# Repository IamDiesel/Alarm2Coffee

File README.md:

# Power on your Philips 2200 Coffeemachine when your smartphone-alarm goes off - via Raspberry Pi and Home-Assistant #
The following readme describes how to setup a raspberry pi / philips 2200 coffeemachine home assistant automation from scratch (incl. setting up home assistant on a Raspberry Pi5). Btw. thanks to https://github.com/TillFleisch/ESPHome-Philips-Smart-Coffee who gave me some inspiration / information on the coffee machine's UART-protocol.
This project is also capable of displaying the current coffeemachine state and remotly operating the coffeemachine via a smartphone's home assistant app:

### Requirements: ###
- Coffee-Machine: Philips 2200
- MITM (inject & passthrough): Inject coffee selection commands and read current coffee configuration
- Use home assistant for automation and hub to the smartphone alarm
- Additional Fail-Safe mechanism in case RPi is dead and  the MITM configuration must be bridged

### Components used: ###
- Raspberry Pi5 + SD Card
- PicoFlex 90325-0008 socket
- Molex 92315-0815, Picoflex, ribbon cable 150mm
- AZDelivery 3 x 4-Relais Modul 5V
- LUCKFOX DSI Capacitive 7 inch Touch Screen with Case
- Jumper Wire / cables / glue / screws / ...
- If Home Assistant should be connected via wifi: Brostrend AX1800 (External USB Wifi Antenna)

## Install home assistant on Raspberry Pi 5 ##
- Use Pi Imager to flash SD card (see https://developbyter.com/home-assistant-auf-raspberry-pi-installieren-und-einrichten/) 
- create empty file called "ssh" on sd card "bootfs"
- tell router to give RPi a constant IP address
- connect via ssh to RPi (ssh user@ipadress)
- update: sudo apt-get update && sudo apt-get upgrade -y
- install dependencies:
  - sudo apt-get install jq wget curl avahi-daemon udisks2 libglib2.0-bin network-manager dbus apparmor -y
  - sudo apt-get install systemd-journal-remote
- reboot: sudo reboot
- deactivate mac address randomisation:
  - sudo nano /etc/NetworkManager/conf.d/100-disable-wifi-mac-randomization.conf
  - Content:

~~~
[connection]
wifi.mac-address-randomization=1
[device]
wifi.scan-rand-mac-address=no
)
~~~

- install docker & add user:
  
~~~
curl -fsSL https://get.docker.com -o get-docker.sh
sudo sh get-docker.sh
docker –version
sudo usermod -aG docker <user>
~~~

- Download OS-Agent on raspberry pi: wget https://github.com/home-assistant/os-agent/releases/download/1.6.0/os-agent_1.6.0_linux_aarch64.deb
- install: sudo dpkg -i os-agent_1.6.0_linux_aarch64.deb

- install additional dependencies:

~~~
sudo apt install \
apparmor \
bluez \
cifs-utils \
curl \
dbus \
jq \
libglib2.0-bin \
lsb-release \
network-manager \
nfs-common \
systemd-journal-remote \
systemd-resolved \
udisks2 \
wget -y
~~~

- install home assistant superviced (https://github.com/home-assistant/supervised-installer/releases/download/2.0.0/homeassistant-supervised.deb)
  - sudo dpkg -i homeassistant-supervised.deb
  - during installation: choose raspberrypi5-64
  - reboot
- open home assistant in your browser: <ipadress_of_pi>:8123
- download and install smartphone app via QR-Code
- Show home assistant on startup on the 7" display:
  - configure autostart: sudo nano /etc/xdg/lxsession/LXDE-pi/autostart
    - add the following lines:
      
~~~
@unclutter
@xset s off
@xset -dpms
@xset s noblank
@chromium-browser --noerrdialogs --check-for-update-interval=31536000 --disable-infobars --kiosk http://127.0.0.1:8123/
~~~
  if you want to keep a 5min display off timer, use the following settings:
~~~
@unclutter
@xset s off
@xset -dpms
@xset s 300 300
@xset s blank
@chromium-browser --noerrdialogs --check-for-update-interval=31536000 --disable-infobars --kiosk http://127.0.0.1:8123/
~~~

  - activate autologin on pi

~~~
cd /usr/share/hassio/homeassistant/
sudo nano configuration.yaml
~~~

  - add the following lines
    
~~~

homeassistant:
  auth_providers:
    - type: homeassistant
    - type: trusted_networks
      trusted_networks:
        - 192.168.2.0/24  # Example network, adjust to your network range
        - fd00::/8
      trusted_users:
        127.0.0.1: 6a24b8e59e2c45328cd1s97ds0b71221  # Map the IP address to the user ID
        192.168.2.43: 6a24b8249e22445x1cd1797123471221  # Map the IP address to the user ID
      allow_bypass_login: true
  ~~~
  
- install 7inch display (https://wiki.luckfox.com/):
  - sudo nano /boot/config.txt
  - add the following lines:
 
~~~
dtoverlay=vc4-kms-v3d
dtoverlay=vc4-kms-dsi-7inch
~~~
## Install Wifi Antenna ##
Installation guide see https://linux.brostrend.com/
For me, the command from the installation guide threw an error.
Command:
~~~
 sh -c 'wget linux.brostrend.com/install -O /tmp/install && sh /tmp/install'
~~~
Error:
~~~
Setting up initramfs-tools (0.142+rpt3+deb12u1) ...
update-initramfs: deferring update (trigger activated)
Processing triggers for initramfs-tools (0.142+rpt3+deb12u1) ...
update-initramfs: Generating /boot/initrd.img-6.6.62+rpt-rpi-v8
mkinitramfs: failed to determine device for /
mkinitramfs: workaround is MODULES=most, check:
grep -r MODULES /etc/initramfs-tools

Error please report bug on initramfs-tools
Include the output of 'mount' and 'cat /proc/mounts'
update-initramfs: failed for /boot/initrd.img-6.6.62+rpt-rpi-v8 with 1.
dpkg: error processing package initramfs-tools (--configure):
 installed initramfs-tools package post-installation script subprocess returned error exit status 1
Errors were encountered while processing:
 initramfs-tools
E: Sub-process /usr/bin/dpkg returned an error code (1)
Aborting, command failed: apt install --reinstall --yes --no-install-recommends ./rtl8852bu-dkms.deb

===================================================
 ERROR: The driver was NOT successfully installed!
===================================================
1) Please select ALL the text in this terminal, then right click with the
   mouse and select Copy, and finally paste all the text in an email to:
   support@brostrend.com
2) Please also attach this autogenerated log file to the email:
   /tmp/troubleshooting.txt
   If you want to view it, run:
   xdg-open /tmp/troubleshooting.txt
3) Some common issues are documented in:
   https://linux.brostrend.com/troubleshooting/
~~~
Solution:
~~~
sudo nano /etc/initramfs-tools/initramfs.conf
~~~
And set „MODULES=dep“ to „MODULES=most“.
Next, the wifi interface needs to be configured:
- deactivate wlan0: sudo ip link set wlan0 down
- Router: remove static ip for old interface and set static ip for the new interface (e.g. 192.168.2.43)
- In Home Assistant: Go to settings->system->network.
  - Reset configuration for wlan0
  - Set static ip for wlan1
- Configure wifi connection:
  - remove all wlan0 profiles (in GUI top right corner, click on the wifi symbol and delete all wlan0 profiles) 
  - sudo nmtui
  - edit connection
  - select wifi->preconficured --> hit "edit"
  - Find the wlan1 device name (for me it is wlxc83a35b569cd (C8:3A:35:B5:69:CD)
  - Enter SSID
  - Enter WIFI-password
  - set manual ip adress: 192.168.2.43/24
  - set Gateway: your routers ip
  - set DNS servers: your routers ip
 
- If chromium doest start on boot: rm -rf ~/.config/chromium/Singleton*

## configure home assistant ##
### Create entities (German) ###
Create entities (Einstellungen -> Geräte und Dienste -> Helfer)

### Create Automations (German) ###

### setup alarm (Android) ###
- Open the Home Assistant App menu and select Settings
- Go to Companion App
- Select Manage Sensors
- Find the Next Alarm sensor
- Enable the Next Alarm sensor
- Create automation: „Einstellungen“->“Automatisierung & Szenen“->“Automatisierung erstellen““Neue Automatisierung“
  - Auslöser hinzufügen: “Andere Auslöser“-->“Template“
  - Template code:
  
   ~~~
    {{(now()+timedelta(0,60)).strftime('%a %h %d %H:%M %Z %Y') == (((state_attr('sensor.pixel_9_pro_next_alarm', 'Time in Milliseconds') | int / 1000) ) | timestamp_custom('%a %h %d %H:%M %Z %Y'))}}
   ~~~
   
  - add action:

### setup alarm (iOs) ###
The focus sensor can be used to determine when the alarm went off.
- Create iOS shortcut named "HAss focus": deactivate focus
- Create iOS automation that executes the "Hass focus" everytime an alarm goes off
Now the companion app focus sensor of the iOS device can be used to trigger automations in Home-Assistant
- Create Home-Assistant automation:

# Disassemble coffee machine #
The coffee machine's display can be disassembled using a plastic tool.

The wiring between display and mainboard is as follows:

Communication is run via UART @115200
The state of the coffeemachine ist sent from the mainboard to the display. The button events are sent from the display to the mainboard.

# Communication #
## Mainboard -> Display

## Display -> Mainboard

### On / Off ###

~~~
On / Off Beep: d5 55 0a 00 00 03 02 00 00 00 32 25
Power on without cleaning cycle: d5 55 01 00 00 03 02 00 00 00 19 10	
Power Off no Cleaning cycle?: d5550000000302010000210c
~~~

### Drink Selection: ###

~~~
Select Nothing: 		d5 55 00 00 00 03 02 00 00 00 2d 01
Select Espresso:	d5 55 00 00 00 03 02 02 00 00 35 1a 	Nachricht wird 13x gesendet
perl -e 'print pack "H*", "d5550000000302020000351a"' > /dev/ttyUSB2

Hot Water:		d5 55 00 00 00 03 02 04 00 00 1d 36
Select Coffee:		d5 55 00 00 00 03 02 08 00 00 05 2b	Nachricht wird 8x gesendet
Steam:			d5 55 00 00 00 03 02 10 00 00 35 11	Nachricht wird 32x gesendet
~~~

### Settings: ###

~~~

d5 55 00 00 00 03 02 00 02 00 35 18	Bean Size
d5 55 00 00 00 03 02 00 04 00 1c 32	Coffee Size
Play:
d5 55 00 00 00 03 02 00 00 01 25 05 	Play-Button (espresso, 39x)
perl -e 'print pack "H*", "d55500000003020000012505"' > /dev/ttyUSB2
~~~

For both mainboard messages and display messages the CRC algorithm is currently unknown. So it might be necessary to record the messages individually.

## Connect relais, UART and power ##

The relayboard 1 is used as a failsafe when the pi does not power on. In that case the UART connection will be without the MITM and therby the mainboard is directly connected to the display. When the relay is activated the raspberry pi acts as MITM between mainboard and display.
Relayboard 2 is used to reset the display when activated via power on command incection. A power cycle will activate the display. This relay is also failsafe for the case, that RPi is powered off, since Display GND is connected to the Relay-Normally-Closed Pin and Relay-Common is connected to the Mainboard GND.
Here is the connection diagram:

## Activate UART2/3 and GPIO on RPi5 & ## 

Add the following lines via "sudo nano /boot/config.txt":

As a result the GPIO configuration will be as follows:
- ttyAMA2	Display	Pin 7 (GPIO 4)	TX
- ttyAMA2	Display	Pin 29 (GPIO 5)	RX
- ttyAMA3	Mainboard	Pin 24 (GPIO 8)	TX
- ttyAMA3	Mainboard	Pin 21 (GPIO 9)	RX

- In order to use GPIO on RPi5 another package is required: .coffee/bin/pip install rpi-lgpio
- It could be necessary to uninstall the RPi GPIO first: .coffee/bin/pip uninstall Rpi.GPIO

## Setup Home Assistant API / install the required python packages ##

- Create a longliving HAss token in HAss: Profil->Sicherheit
  - safe this token in a file called "HASS_Token.py" with: token = "asdjalksdjkasjdklasjd your token asdlkalösdkaölsd"
- Create venv:  python3 -m venv .coffee
- install Home assistant: .coffee/bin/pip install homeassistant_api
- install pyserial: .coffee/bin/pip install pyserial

## Home Assistant WIFI Stability Issues ##
Home Assistant started beeing offline from time to time. Where the device was not reachable via ssh or the home assistant app.
The only thing that seemed to help was a wifi reset. So I wrote a little script that (e.g.) pings the local router. In case the router is not reachable the script will reset wifi, making the HAss available again.

## Finish ##

- Thats it. Now run Philips_2200.py and the RPI will inject the respective display commands, when the respective Home Assistant buttons are pushed. If no button is pushed, the RPi will forward all messages from display to mainboard and vice versa. In Addition a alarm will trigger a power on command sent to the coffee machine.
- the relay boards fit nicely behind the display. I glued screws on the backside of the display module in order to fit the relay boards to the display.
- In order to run the python script on startup the following lines can be added to rc.local via sudo nano /etc/rc.local:
~~~
sudo bash -c '/home/youruser/.coffee/bin/python3 /home/youruser/Documents/philips_pi/Philips_2200.py > /home/fuchsi/Documents/philips_pi/alarm2coffee.log 2>&1' &
~~~
Of course the path must be set to your local Philips_2200.py. In addition Wifi_Reset.py must be in the same folder as Philips_2200.py.
- Also a dashboard can be created in order to interact with the coffeemachine via smartphone. Here is mine:

~~~

views:
  - type: sections
    max_columns: 2
    title: Kaffee
    path: kaffee
    icon: mdi:coffee
    sections:
      - type: grid
        cards:
          - type: tile
            entity: input_button.philips_display_power_btn
            name: Power On
            icon_tap_action:
              action: toggle
            tap_action:
              action: toggle
            hide_state: true
          - type: tile
            entity: input_button.philips_display_power_off_btn
            name: Power Off
            tap_action:
              action: toggle
            hide_state: true
          - show_name: true
            show_icon: true
            type: button
            tap_action:
              action: perform-action
              perform_action: automation.trigger
              target:
                entity_id: automation.philips_display_steam_event_helper
              data:
                skip_condition: true
            entity: input_boolean.philips_mainboard_espresso_led
            show_state: false
            name: Espresso
            icon: mdi:cup
          - show_name: true
            show_icon: true
            type: button
            tap_action:
              action: perform-action
              perform_action: automation.trigger
              target:
                entity_id: automation.philips_event_coffee_btn
              data:
                skip_condition: true
            entity: input_boolean.philips_mainboard_coffee_led
            show_state: false
            name: Coffee
            icon: mdi:coffee
          - show_name: true
            show_icon: true
            type: button
            tap_action:
              action: perform-action
              perform_action: automation.trigger
              target:
                entity_id: automation.philips_event_hot_water_btn
              data:
                skip_condition: true
            entity: input_boolean.philips_mainboard_hot_water_led
            show_state: false
            name: Hot Water
            icon: mdi:tea-outline
          - show_name: true
            show_icon: true
            type: button
            tap_action:
              action: perform-action
              perform_action: automation.trigger
              target:
                entity_id: automation.neue_automatisierung
              data:
                skip_condition: true
            entity: input_boolean.philips_mainboard_steam_led
            show_state: false
            name: Steam
            icon: mdi:weather-windy
      - type: grid
        cards:
          - show_name: true
            show_icon: true
            type: button
            tap_action:
              action: toggle
            entity: input_button.input_button_philips_display_play_btn
            grid_options:
              columns: 12
              rows: 2
            name: Start
          - type: conditional
            conditions:
              - condition: state
                entity: input_select.philips_bean_led
                state: '1'
            grid_options:
              columns: 6
              rows: 1
            card:
              show_name: true
              show_icon: true
              type: button
              tap_action:
                action: toggle
              entity: input_button.philips_display_bean_btn
              icon: mdi:network-strength-1
              hold_action:
                action: toggle
              name: Strength
          - type: conditional
            conditions:
              - condition: state
                entity: input_select.philips_bean_led
                state: '2'
            grid_options:
              columns: 6
              rows: 1
            card:
              show_name: true
              show_icon: true
              type: button
              tap_action:
                action: toggle
              entity: input_button.philips_display_bean_btn
              icon: mdi:network-strength-3
              hold_action:
                action: toggle
              name: Strength
          - type: conditional
            conditions:
              - condition: state
                entity: input_select.philips_bean_led
                state: '3'
            grid_options:
              columns: 6
              rows: 1
            card:
              show_name: true
              show_icon: true
              type: button
              tap_action:
                action: toggle
              entity: input_button.philips_display_bean_btn
              icon: mdi:network-strength-4
              hold_action:
                action: toggle
              name: Strength
          - type: conditional
            conditions:
              - condition: state
                entity: input_select.philips_bean_led
                state: 'Off'
            grid_options:
              columns: 6
              rows: 1
            card:
              show_name: true
              show_icon: true
              type: button
              tap_action:
                action: none
              entity: input_button.philips_display_bean_btn
              icon: mdi:cancel
              hold_action:
                action: none
              name: Strength
          - type: conditional
            conditions:
              - condition: state
                entity: input_select.philips_cup_size_led
                state: '1'
            grid_options:
              columns: 6
              rows: 1
            card:
              show_name: true
              show_icon: true
              type: button
              tap_action:
                action: toggle
              entity: input_button.philips_display_cup_btn
              icon: mdi:network-strength-1
              hold_action:
                action: toggle
              name: Size
          - type: conditional
            conditions:
              - condition: state
                entity: input_select.philips_cup_size_led
                state: '2'
            grid_options:
              columns: 6
              rows: 1
            card:
              show_name: true
              show_icon: true
              type: button
              tap_action:
                action: toggle
              entity: input_button.philips_display_cup_btn
              icon: mdi:network-strength-3
              hold_action:
                action: toggle
              name: Size
          - type: conditional
            conditions:
              - condition: state
                entity: input_select.philips_cup_size_led
                state: '3'
            grid_options:
              columns: 6
              rows: 1
            card:
              show_name: true
              show_icon: true
              type: button
              tap_action:
                action: toggle
              entity: input_button.philips_display_cup_btn
              icon: mdi:network-strength-4
              hold_action:
                action: toggle
              name: Size
          - type: conditional
            conditions:
              - condition: state
                entity: input_select.philips_cup_size_led
                state: 'Off'
            grid_options:
              columns: 6
              rows: 1
            card:
              show_name: true
              show_icon: true
              type: button
              tap_action:
                action: none
              entity: input_button.philips_display_cup_btn
              icon: mdi:cancel
              hold_action:
                action: none
              name: Size
          - type: conditional
            conditions:
              - condition: state
                entity: input_boolean.philips_double_coffee_led
                state: 'on'
            grid_options:
              columns: 6
              rows: 1
            card:
              show_name: true
              show_icon: true
              type: button
              tap_action:
                action: none
              entity: input_boolean.philips_double_coffee_led
              name: Coffee
              hold_action:
                action: none
              icon: mdi:dice-2
          - type: conditional
            conditions:
              - condition: state
                entity: input_boolean.philips_double_espresso_led
                state: 'on'
            grid_options:
              columns: 6
              rows: 1
            card:
              show_name: true
              show_icon: true
              type: button
              tap_action:
                action: none
              entity: input_boolean.philips_double_coffee_led
              name: Espresso
              hold_action:
                action: none
              icon: mdi:dice-2
          - type: conditional
            conditions:
              - condition: state
                entity: input_select.philipps_water_empty_led
                state: Water empty
            grid_options:
              columns: 6
              rows: 1
            card:
              show_name: true
              show_icon: true
              type: button
              tap_action:
                action: none
              entity: input_select.philipps_water_empty_led
              name: No Water
              hold_action:
                action: none
              icon: mdi:water-off
          - type: conditional
            conditions:
              - condition: state
                entity: input_select.philipps_error_led
                state: Waste full
            grid_options:
              columns: 6
              rows: 1
            card:
              show_name: true
              show_icon: true
              type: button
              tap_action:
                action: none
              entity: input_boolean.philips_waste_helper_led
              name: Waste full
              hold_action:
                action: none
              icon: mdi:delete-variant
          - type: conditional
            conditions:
              - condition: state
                entity: input_select.philipps_error_led
                state: Error active
            grid_options:
              columns: 6
              rows: 1
            card:
              show_name: true
              show_icon: true
              type: button
              tap_action:
                action: none
              entity: input_boolean.philips_error_helper_led
              name: Error
              hold_action:
                action: none
              icon: mdi:alert-circle
        column_span: 1
      - type: grid
        cards:
          - type: heading
            heading_style: title
            icon: mdi:alarm
            badges:
              - type: entity
                entity: input_boolean.philips_alarm_daniel
              - type: entity
                entity: sensor.pixel_9_pro_next_alarm
              - type: entity
                show_state: true
                show_icon: true
                entity: input_boolean.philips_alarm_fox
            heading: Mit Wecker einschalten
          - type: tile
            entity: input_boolean.philips_alarm_daniel
            tap_action:
              action: toggle
            name: Alarm2Coffee Daniel
            grid_options:
              columns: 12
              rows: 1
          - type: tile
            entity: input_boolean.philips_alarm_fox
            tap_action:
              action: toggle
            name: Alarm2Coffee Fox
            grid_options:
              columns: 12
              rows: 1
          - type: tile
            entity: sensor.pixel_9_pro_next_alarm
            grid_options:
              columns: 12
              rows: 2
            name: Nächster Wecker Daniel
            hide_state: false
            show_entity_picture: false
            vertical: true
            state_content:
              - state
              - Local Time

~~~

# TODOs #
- [ ] Create relay-circuit-board to avoid messy wiring (also 3 relays are unused)
- [ ] Refactor python software
  - [x] check for HAss availability on startup
  - [ ] refactor SW components (file / component is too big)
  - [ ] further evaluate power cycle code
  - [x] Read coffee strength and display this information in home assistant
  - [x] Read cup size and display this information in home assistant
  - [x] Read 1x / 2x and drink selection information and display this information in home assistant
  - [x] Check Home Assistant loosing WIFI connection to home net
    - [x] Write script to reset wifi when loosing connection to gateway
    - [x] evaluate power settings

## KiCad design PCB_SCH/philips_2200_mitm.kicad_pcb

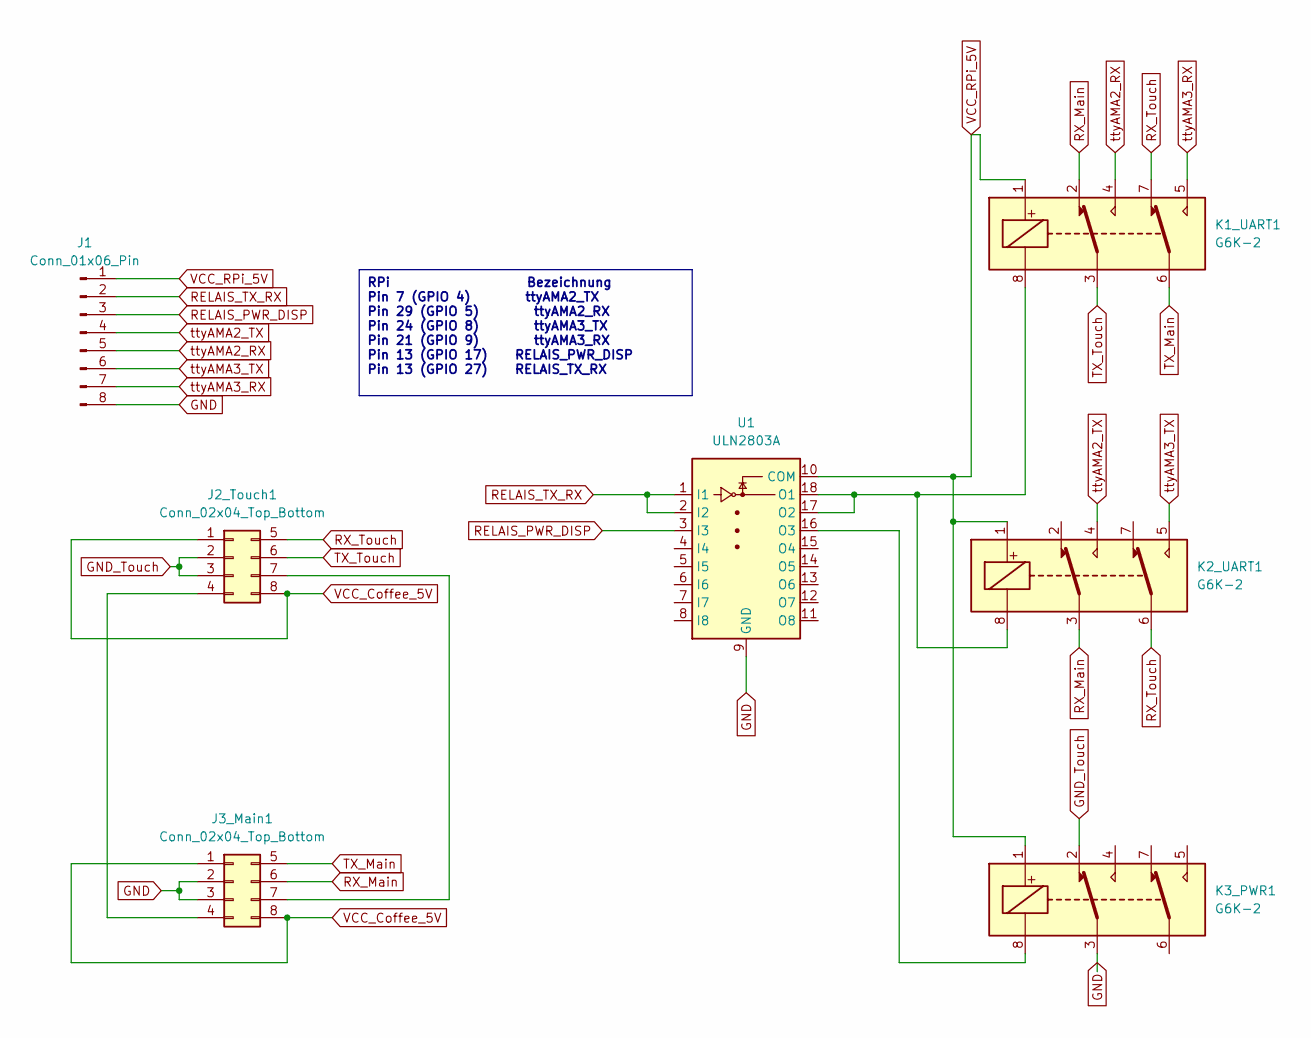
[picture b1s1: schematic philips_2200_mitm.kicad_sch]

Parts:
J1: Conn_01x06_Pin; PinHeader_1x08_P2.54mm_Horizontal
J2_Touch1, J3_Main1: Conn_02x04_Top_Bottom; Molex_Picoflex_90325-0008_2x04_P1.27mm_Vertical
K1_UART1, K2_UART1, K3_PWR1: G6K-2; Relay_DPDT_Omron_G6K-2F-Y
U1: ULN2803A; SOIC-18W_7.5x11.6mm_P1.27mm

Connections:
GND: J1.8, J3_Main1.2, J3_Main1.3, K3_PWR1.3, U1.9 (GND)
GND_Touch: J2_Touch1.2, J2_Touch1.3, K3_PWR1.2
unnamed: J2_Touch1.4, J3_Main1.4
unnamed: J2_Touch1.7, J3_Main1.7
unnamed: K1_UART1.8, K2_UART1.8, U1.17 (O2), U1.18 (O1)
unnamed: K3_PWR1.8, U1.16 (O3)
RELAIS_PWR_DISP: J1.3, U1.3 (I3)
RELAIS_TX_RX: J1.2, U1.1 (I1), U1.2 (I2)
RX_Main: J3_Main1.6, K1_UART1.2, K2_UART1.3
RX_Touch: J2_Touch1.5, K1_UART1.7, K2_UART1.6
TX_Main: J3_Main1.5, K1_UART1.6
TX_Touch: J2_Touch1.6, K1_UART1.3
VCC_Coffee_5V: J2_Touch1.1, J2_Touch1.8, J3_Main1.1, J3_Main1.8
VCC_RPi_5V: J1.1, K1_UART1.1, K2_UART1.1, K3_PWR1.1, U1.10 (COM)
ttyAMA2_RX: J1.5, K1_UART1.4
ttyAMA2_TX: J1.4, K2_UART1.4
ttyAMA3_RX: J1.7, K1_UART1.5
ttyAMA3_TX: J1.6, K2_UART1.5

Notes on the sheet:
RPi Bezeichnung Pin 7 (GPIO 4) ttyAMA2_TX Pin 29 (GPIO 5) ttyAMA2_RX Pin 24 (GPIO 8) ttyAMA3_TX Pin 21 (GPIO 9) ttyAMA3_RX Pin 13 (GPIO 17) RELAIS_PWR_DISP Pin 13 (GPIO 27) RELAIS_TX_RX

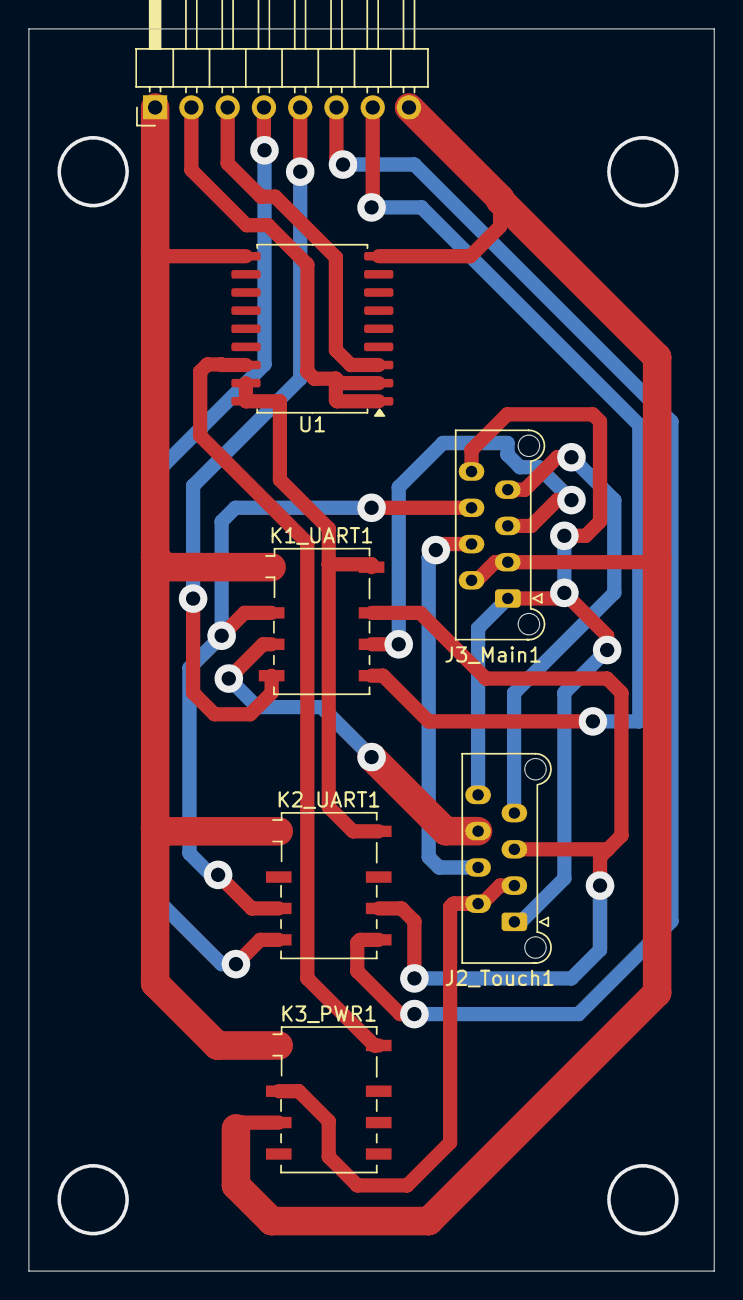
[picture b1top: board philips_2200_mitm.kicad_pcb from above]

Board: 2 copper layers, 48.0 x 87.0 mm, 7 parts (0 on the bottom side), 18 nets.

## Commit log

2024-12-26 Exploring
    Parsing messages comming from the mainboard
2024-12-30 serial passtrough and display in HA
2024-12-30 get devicename of serialadapter
2024-12-31 select drink via home assistant
2025-01-07 Added GPIO for relais new machine commands
2025-01-09 Mainboard power reset ugly but working
2025-01-10 Minor cleanup
2025-01-12 File is executed after Pi boot
2025-01-13 add folder
2025-01-16 Initial commit
    can be used to reset WIFI Connection which can be unstable on HAss RPi
2025-01-17 Fix Home Assistant WIFI stability issues
2025-01-17 Integrate Wifi reset
2025-01-17 Wait for API on startup
2025-01-20 Set Waste, Cup Size, coffee strength & error LEDs
2025-01-20 power on with cleaning cycle
2025-01-20 Use WifiDeamon
2025-01-23 reset wifi: full device activation
2025-01-31 Wifi stable
2025-03-17 Untested PCB + Schematic
2025-03-17 untested pcb + sch
